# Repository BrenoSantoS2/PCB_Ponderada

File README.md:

## Ponderada: Entrega de PCB
### Organização do repositório:
**Pasta Ponderada-backups:** Backups feitos automaticamente pelo Kicad (Não tenho certeza, preferi não mexer)

**Pasta Gerber:** Possui todos os arquivos .gbr criados pelo KiCad

**Ponderada.kicad_pcb:** Arquivo PCB do projeto

**Ponderada.kicad_sch:** Desenho esquemático do projeto

**Ponderada.kicad_pro:** Arquivo de inicialização do KiCad (Ou algo do tipo)

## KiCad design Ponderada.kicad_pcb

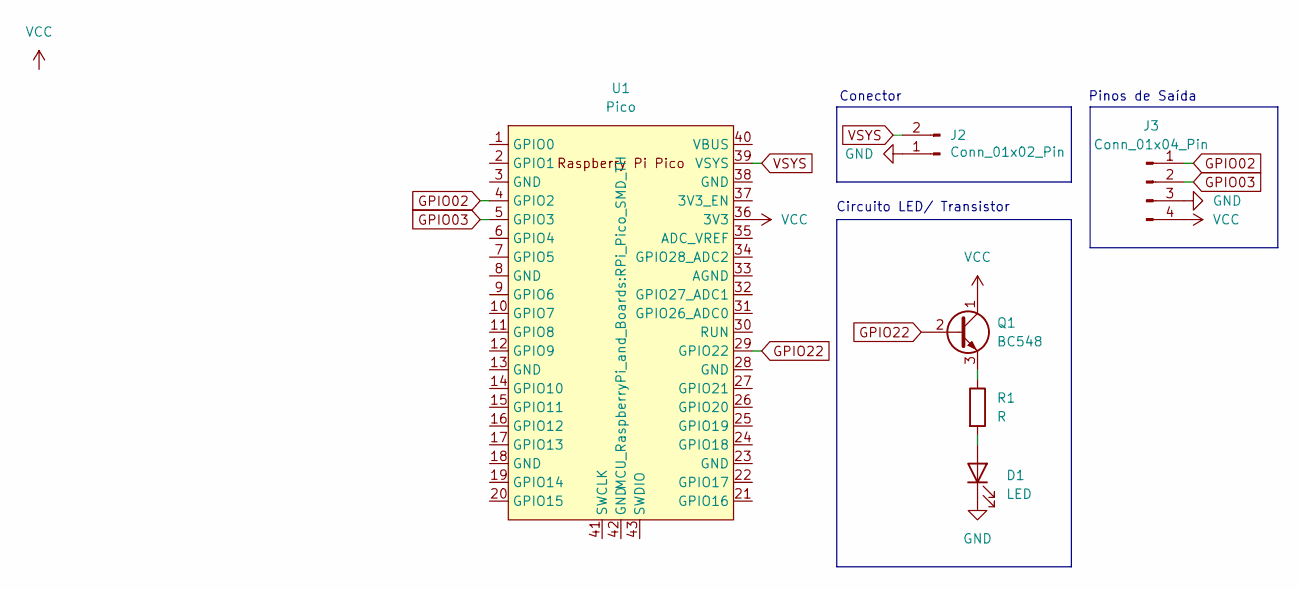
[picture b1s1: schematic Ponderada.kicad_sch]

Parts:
D1: LED; LED_D5.0mm_FlatTop
J2: Conn_01x02_Pin; PinSocket_1x02_P1.27mm_Vertical
J3: Conn_01x04_Pin; PinHeader_1x04_P1.00mm_Vertical
Q1: BC548; TO-92_Inline
R1: R; R_Axial_DIN0204_L3.6mm_D1.6mm_P5.08mm_Horizontal
U1: Pico; RPi_Pico_SMD_TH

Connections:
GND: D1.1 (K), J2.1, J3.3
GPIO02: J3.1, U1.4 (GPIO2)
GPIO03: J3.2, U1.5 (GPIO3)
GPIO22: Q1.2 (B), U1.29 (GPIO22)
unnamed: D1.2 (A), R1.2
unnamed: Q1.3 (E), R1.1
VCC: J3.4, Q1.1 (C), U1.36 (3V3)
VSYS: J2.2, U1.39 (VSYS)

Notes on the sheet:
Pinos de Saída
Conector
Circuito LED/ Transistor

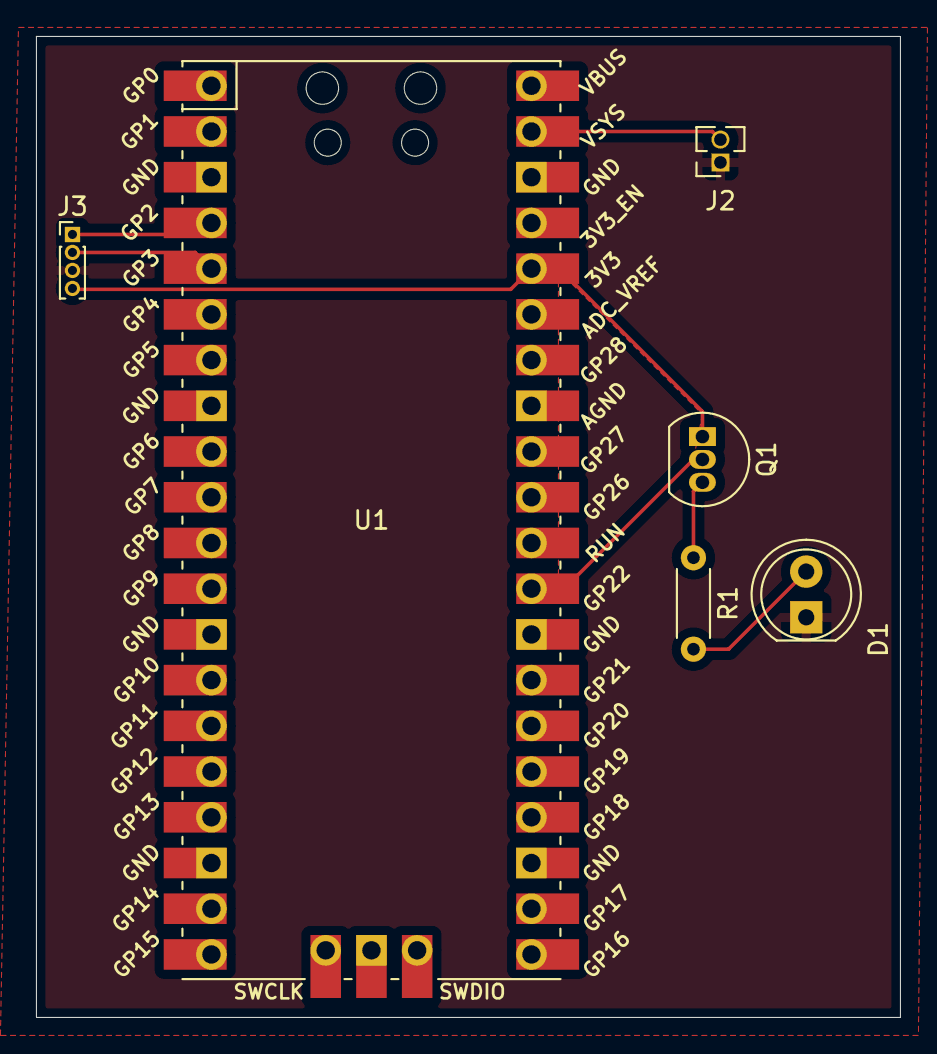
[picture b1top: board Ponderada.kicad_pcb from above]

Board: 2 copper layers, 48.0 x 54.5 mm, 6 parts (0 on the bottom side), 8 nets.

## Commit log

2024-03-30 Finalizando
